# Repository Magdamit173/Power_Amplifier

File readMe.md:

# Multi-Stage BJT Power Amplifier (v1.1)

A high-gain, dual-stage BJT amplifier project designed for the **Stage I (Feb 26)** milestone. This design is optimized for fabrication on a **presensitized PCB** with a compact footprint.

### Design Specifications
* **Target Gain ($A_v$):** $\ge 120$
* **Frequency Range (Ideal):** $80\text{Hz}$ to $20\text{kHz}$
* **Board Dimensions:** $2.18 \times 1.09$ inches
* **Trace Clearance:** $0.200\text{mm}$ ~ $0.400\text{mm}$ 
* **Track Width:** $0.8\text{mm}$ ~$1.0\text{mm}$
* **Fabrication Method:** Presensitized PCB

### Component Notes
* **Coupling Capacitors:** 10µF 50V **Monolithic Ceramics** (Code 106).
* **Bypass Capacitors:** 33µF **16V** Electrolytics.
* **Note:** Monolithic capacitors are utilized in this design as the primary representation for high-value ceramic components to ensure a compact and stable PCB layout.

### Components (Table of Expense)

| Category | Component Description | Qty | Unit Price (PHP) | Total (PHP) | Reference Link |
| :--- | :--- | :---: | :---: | :---: | :--- |
| **Active** | BC547 NPN Transistor (Unsorted) | 1 | ₱0.83 | ₱0.83 | [Shopee (100pcs)](https://shopee.ph/100pcs-BC547-TO-92-NPN-transistor-i.119376932.27625517704) |
| **Active** | 2N3904 NPN Transistor | 1 | ₱0.96 | ₱0.96 | [Shopee (50pcs)](https://shopee.ph/50PCS-2N3904-2N3906-2N4403-2N2907-2N4401-2N2222-PN2222-2N5401-2N5551-TO-92-TO92-Transistor-New-i.1130255612.20395632930) |
| **Capacitors** | 10µF 50V Monolithic Ceramic (106) | 3 | ₱0.98 | ₱2.94 | [Shopee (50pcs)](https://shopee.ph/product/497215439/24193377802) |
| **Capacitors** | 33µF 16V Electrolytic | 2 | ₱3.60 | ₱7.20 | [Shopee (5pcs)](https://shopee.ph/Electrolytic-Capacitor-16V-25V-35V-50V-i.535662606.26003134704) |
| **Resistors** | 1/4W Metal Film Resistors | 11 | ₱3.00 | ₱33.00 | Local Retail |
| **Connectors** | 2-Pin Screw Terminal (5.0mm) | 3 | ₱4.20 | ₱12.60 | [Shopee (10pcs)](https://shopee.ph/10Pcs-KF301-2P-Screw-5.0mm-Terminal-Block-i.487295469.12046517038) |
| **Fabrication**| **Presensitized PCB (4x6 inches)** | 1 | **₱205.00** | **₱205.00** | [Lazada (Alexan)](https://www.lazada.com.ph/products/with-developer-alexan-presensitized-pcb-4x6-i1380024544.html) |
| **TOTAL** | | | | **₱261.53** | |

*Note: Unit prices are derived from bulk pack listings (Shopee/Lazada) to reflect actual prototype cost.*

### Design Documentation

#### Schematic Diagram

### PCB Layout & 3D Preview
| 2D Copper Trace View | 3D Rendered View |
| :--- | :--- |
|  |  |

### Repository Structure
* **`/Plot`**: Contains exported manufacturing files (SVG/PNG).

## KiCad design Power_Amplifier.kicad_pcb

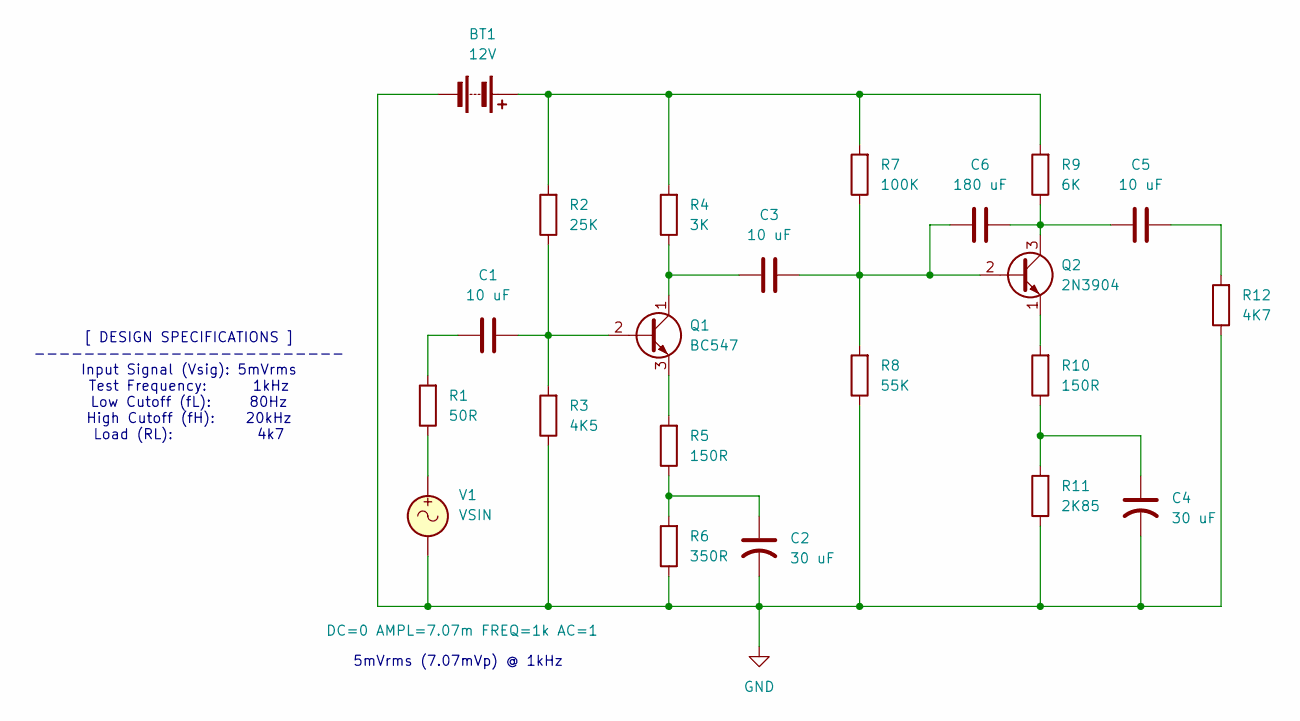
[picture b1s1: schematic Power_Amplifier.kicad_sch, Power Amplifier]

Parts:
BT1: 12V; TerminalBlock_Phoenix_MKDS-1,5-2_1x02_P5.00mm_Horizontal
C1, C3, C5: 10 uF; C_Disc_D5.1mm_W3.2mm_P5.00mm
C2, C4: 30 uF; CP_Radial_D5.0mm_P2.00mm
C6: 180 uF; C_Disc_D4.3mm_W1.9mm_P5.00mm
Q1: BC547; TO-92_Inline
Q2: 2N3904; TO-92_Inline
R1: 50R; R_Axial_DIN0207_L6.3mm_D2.5mm_P10.16mm_Horizontal
R2: 25K; R_Axial_DIN0207_L6.3mm_D2.5mm_P10.16mm_Horizontal
R3: 4K5; R_Axial_DIN0207_L6.3mm_D2.5mm_P10.16mm_Horizontal
R4: 3K; R_Axial_DIN0207_L6.3mm_D2.5mm_P10.16mm_Horizontal
R5, R10: 150R; R_Axial_DIN0207_L6.3mm_D2.5mm_P10.16mm_Horizontal
R6: 350R; R_Axial_DIN0207_L6.3mm_D2.5mm_P10.16mm_Horizontal
R7: 100K; R_Axial_DIN0207_L6.3mm_D2.5mm_P10.16mm_Horizontal
R8: 55K; R_Axial_DIN0207_L6.3mm_D2.5mm_P10.16mm_Horizontal
R9: 6K; R_Axial_DIN0207_L6.3mm_D2.5mm_P10.16mm_Horizontal
R11: 2K85; R_Axial_DIN0207_L6.3mm_D2.5mm_P10.16mm_Horizontal
R12: 4K7; TerminalBlock_Phoenix_MKDS-1,5-2_1x02_P5.00mm_Horizontal
V1: VSIN; TerminalBlock_Phoenix_MKDS-1,5-2_1x02_P5.00mm_Horizontal

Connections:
GND: BT1.2 (-), C2.2, C4.2, R3.1, R6.1, R8.1, R11.1, R12.1, V1.2
unnamed: BT1.1 (+), R2.2, R4.2, R7.2, R9.2
unnamed: C1.1, R1.2
unnamed: C2.1, R5.1, R6.2
unnamed: C4.1, R10.1, R11.2
unnamed: C5.1, R12.2
unnamed: C1.2, Q1.2 (B), R2.1, R3.2
unnamed: C3.1, Q1.1 (C), R4.1
unnamed: Q1.3 (E), R5.2
unnamed: C3.2, C6.2, Q2.2 (B), R7.1, R8.2
unnamed: C5.2, C6.1, Q2.3 (C), R9.1
unnamed: Q2.1 (E), R10.2
unnamed: R1.1, V1.1

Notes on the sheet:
[ DESIGN SPECIFICATIONS ] ------------------------- Input Signal (Vsig): 5mVrms Test Frequency: 1kHz Low Cutoff (fL): 80Hz High Cutoff (fH): 20kHz Load (RL): 4k7
5mVrms (7.07mVp) @ 1kHz

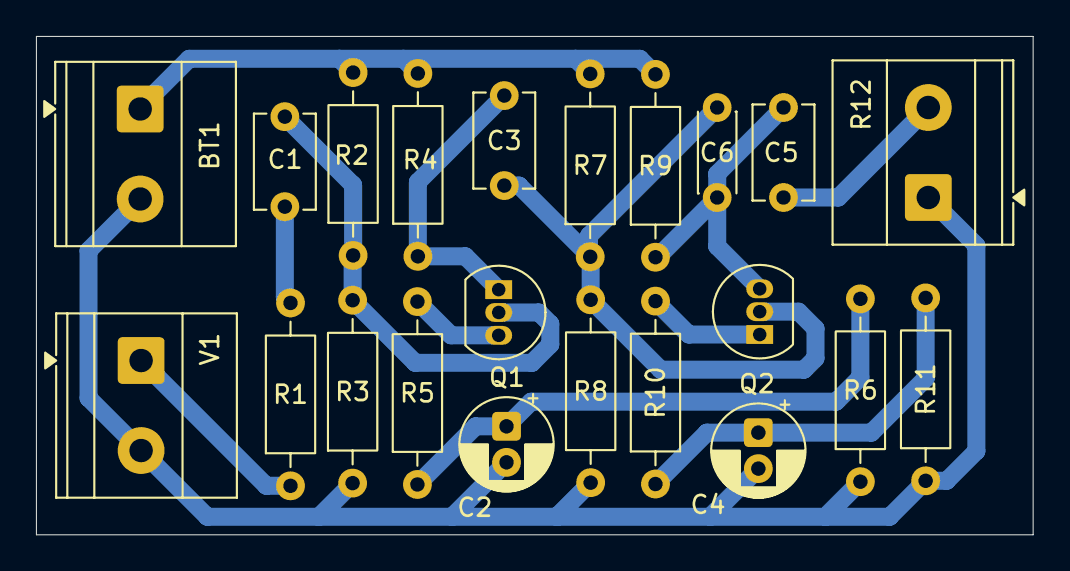
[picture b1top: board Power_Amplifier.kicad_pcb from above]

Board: 2 copper layers, 55.4 x 27.7 mm, 22 parts (0 on the bottom side), 13 nets.

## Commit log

2026-02-26 version 1.1: 2.26.2026
